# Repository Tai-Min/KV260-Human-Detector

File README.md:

# KV260-Human-Detector
Lidar based human detector on Kria KV260.

Created for [Adaptive Computing Challenge 2021
with Xilinx](https://www.hackster.io/contests/xilinxadaptivecomputing2021).

For more information about the project itself see [Human position estimator for mobile robots](https://www.hackster.io/Tai-Min/human-position-estimator-for-mobile-robots-d86454).

This repository contains all files and instructions required to recreate the project from scratch, including code, hardware design files, PCB design and 3D printable parts. 

# Recreating the project
## PCB shield

Use included in \<REPO>/pmod_shield/grbl Gerber files to order the shield using some PCB manufacturing service, or use included \<REPO>/pmod_shield/pcb.pdf to [etch it by yourself](https://www.instructables.com/How-to-Etch-a-PCB/).

For the parts you will need:
* 1x A4988 stepper motor driver,
* 2x 2 pin female JST PCB connectors,
* 1x 4 pin female JST PCB connector or 4x1 male vertical goldpin connector, whatever fits your stepper motor better,
* 1x 2x6 pin male horizontal goldpin connector,
* 2x 8x1 female vertical goldpin connectors,
* 1x 5.08mm screw terminal block

Solder the parts as in the picture below (ignore crossed parts):

## Attaching hardware
Print listed below parts (from \<REPO>/stl):
* 1x bottom_panel
* 1x bottom_panel_stopper
* 2x bottom_panel_feets
* 2x lidar_frame
* 1x motor_frame
* 2x top_panel
* 1x cradle
* lidar_board_holder
* 1x nema_connector

1) Screw 3D printed parts using M3 15mm screws,
2) Insert 608 bearings into bearing holes of lidar_frames,
3) Slide 190mm threaded rod through bearings and cradle (with M8 nuts inserted) into nema_connector,
5) Using M3 15mm screws and corresponding nuts, screw NEMA17 stepper motor, Creality endstops and YDlidar X4 
6) Slide KV260 into the frame,
7) Connect LIDAR through it's UART board to one of KV260's USB ports, 
8) Connect PMod shield to KV260 and then connect stepper motor and endstops to the shield.
9) Connect KV260 to PC and to local network using Ethernet connector.

Use these images for reference:

## Building the software
Project created and tested using Ubuntu-20.04.

This repo's root directory is from now onwards called \<REPO>

### Prerequisites

This instruction assumes that Vitis software (Vivado, Vitis, Vitis-AI, PetaLinux) runs on version 2021.1 and is correctly sourced in ".bashrc". It also assumes that PetaLinux has installed all [required packages](https://www.xilinx.com/support/documentation/sw_manuals/xilinx2020_1/ug1144-petalinux-tools-reference-guide.pdf).

For SD flashing [balenaEtcher](https://www.balena.io/etcher/) will be used.

Also, there are additional packages that should be installed via apt:
- putty
- sshpass (OPTIONAL used in build_app.sh with -p option provided to ignore multiple petalinux password inputs, considered bad practice so use at your own risk)

### Regenerate project

1. In Vivado open hardware project \<REPO>/hardware/hardware.xpr and press Generate Bitstream

Considering that build files for PetaLinux and it's SDK take roughly 60Gb of space, I don't think than anyone would want to download and extract such blob of files (also GitHub would be mad at me I guess). So to create this project locally I have provided simple script that builds everything from scratch up to the Vitis platform.

2. In terminal, in \<REPO>/ run:
```
chmod +x ./regenerate_hw.sh && ./regenerate_hw.sh
```
This script will:
- export hardware design (XSA file)
- generate and compile device tree overlay (DTO)
- compile pre-configured PetaLinux image, it's SDK and unpack it to Vitis workspace directory
- create .wic image for SD card
- update Vitis platform with new hardware description and linux image

3. Flash \<REPO>/linux/images/linux/petalinux-sdimage.wic into SD card (i.e using balenaEtcher)

4. Verify whether everything is working via Putty and set new petalinux's password (called \<DEVPWD> onwards):
```
sudo putty /dev/ttyUSBn -serial -sercfg 115200,8,n,1,N
```
replace "n" in "/dev/ttyUSBn" with correct USB number that responds with PetaLinux booting process.

Before leaving PetaLinux's shell, check device's ip with 
```
ifconfig
```
Write down address near "inet" under "eth0". This address will be called \<DEVIP> from now onwards.

### Build project
1. a) Only to build the application, in terminal, in \<REPO>/ run:
```
chmod +x ./build_app.sh && ./build_app.sh
```
This will generate all necessary files in \<REPO>/package/app/final

1. b) To build and upload to the device:
```
chmod +x ./build_app.sh && ./build_app.sh -u petalinux@<DEVIP>
```
This method will ask for petalinux's password multiple times.
1. c) (sshpass required!) To build and upload to the device:
```
chmod +x ./build_app.sh && ./build_app.sh -u petalinux@<DEVIP> -p <DEVPWD>
```
This method will ask for petalinux's password once.

### Run the application
1. a) SSH into KV260:
```
ssh petalinux@<DEVIP>
```

1. b) Use Putty terminal from previous steps.

2. Run:
```
sudo su
source ./setup.sh
./smart_lidar
```
* Sudo is required to use xmutil and access /lib folder.
* source.sh will setup FPGA bitstream and source ROS2 into our environment
* smart_lidar will start the application.

### Troubleshoting
If PetaLinux does not build due to error in Vitis-AI meta package, try to remove "dnndk" package from \<REPO>/linux/components/yocto/layers/meta-petalinux/recipes-core/packagegroups/packagegroup-petalinux-vitisai.bb

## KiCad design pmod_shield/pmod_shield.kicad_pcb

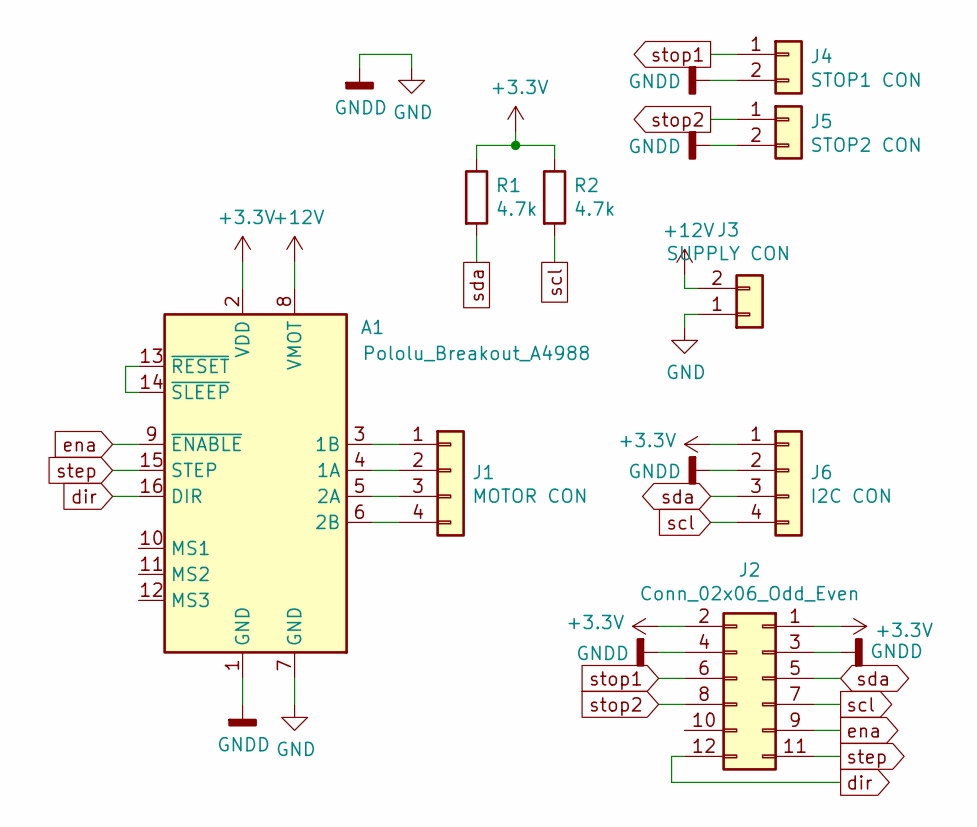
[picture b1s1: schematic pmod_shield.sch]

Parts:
A1: Pololu_Breakout_A4988; Pololu_Breakout-16_15.2x20.3mm
J1: MOTOR CON; PinHeader_1x04_P2.54mm_Vertical
J2: Conn_02x06_Odd_Even; PinHeader_2x06_P2.54mm_Horizontal
J3: SUPPLY CON; PhoenixContact_MSTBA_2,5_2-G-5,08_1x02_P5.08mm_Horizontal
J4: STOP1 CON; JST_XH_B2B-XH-AM_1x02_P2.50mm_Vertical
J5: STOP2 CON; JST_XH_B2B-XH-AM_1x02_P2.50mm_Vertical
J6: I2C CON; JST_XH_B4B-XH-AM_1x04_P2.50mm_Vertical
R1, R2: 4.7k; R_Axial_DIN0204_L3.6mm_D1.6mm_P7.62mm_Horizontal

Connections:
+3V3: A1.2 (VDD), J2.1, J2.2, J6.1, R1.1, R2.1
+12V: A1.8 (VMOT), J3.2
GND: A1.1 (GND), A1.7 (GND), J2.3, J2.4, J3.1, J4.2, J5.2, J6.2
unnamed: A1.3 (1B), J1.1
unnamed: A1.4 (1A), J1.2
unnamed: A1.5 (2A), J1.3
unnamed: A1.6 (2B), J1.4
unnamed: A1.13 (~RESET), A1.14 (~SLEEP)
dir: A1.16 (DIR), J2.12
ena: A1.9 (~ENABLE), J2.9
scl: J2.7, J6.4, R2.2
sda: J2.5, J6.3, R1.2
step: A1.15 (STEP), J2.11
stop1: J2.6, J4.1
stop2: J2.8, J5.1

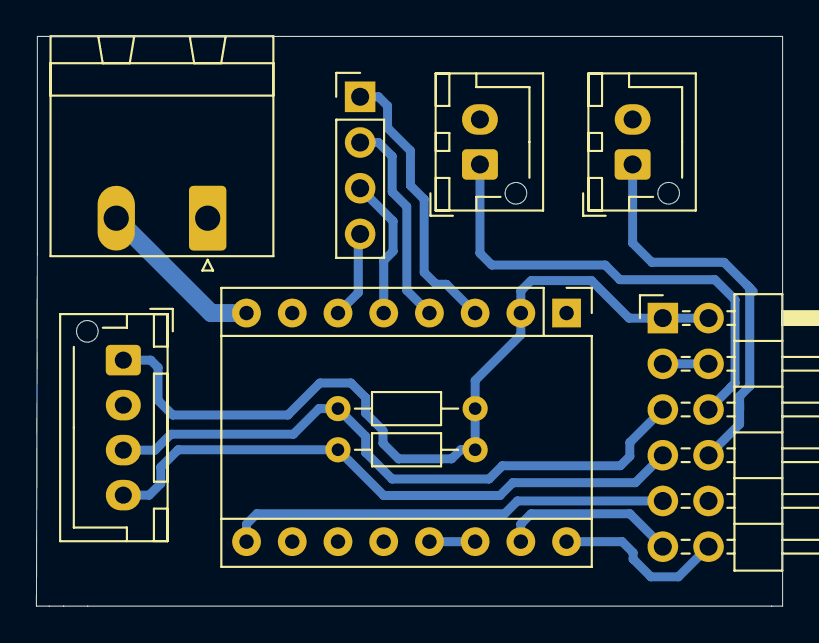
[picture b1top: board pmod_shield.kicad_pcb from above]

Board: 2 copper layers, 41.5 x 31.6 mm, 9 parts (0 on the bottom side), 15 nets.

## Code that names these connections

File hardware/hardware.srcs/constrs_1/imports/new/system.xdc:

set_property PACKAGE_PIN B11 [get_ports stop1]
set_property IOSTANDARD LVCMOS33 [get_ports stop1]
set_property PULLTYPE PULLUP [get_ports stop1]

set_property PACKAGE_PIN D11 [get_ports stop2]
set_property IOSTANDARD LVCMOS33 [get_ports stop2]
set_property PULLTYPE PULLUP [get_ports stop2]

set_property PACKAGE_PIN H12 [get_ports step]
set_property IOSTANDARD LVCMOS33 [get_ports step]

set_property PACKAGE_PIN B10 [get_ports dir]
set_property IOSTANDARD LVCMOS33 [get_ports dir]

set_property PACKAGE_PIN E10 [get_ports ena]
set_property IOSTANDARD LVCMOS33 [get_ports ena]

set_property PACKAGE_PIN A12 [get_ports fan]
set_property IOSTANDARD LVCMOS33 [get_ports fan]

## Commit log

2022-01-09 Create HW design
2022-01-09 Add linux conf
2022-01-09 Work on build script, generate FPGA bitstream
2022-01-09 Work on build_linux.ps1 script
2022-01-12 Add build_app.ps1, work on regenerate_hw.ps1
2022-01-18 Moving to linux
2022-01-18 Move to linux
2022-01-18 Modify gitignore
2022-01-18 Fix ignores
2022-01-18 Remove files
2022-02-01 Move HW design to Vivado 2020.2 for KRS stack
2022-02-07 Env setup for project
2022-02-07 Control stepper from app
2022-02-07 Add ydlidar sdk
2022-02-10 Add USB Hub to DeviceTree
2022-02-13 Add working PointCloud2 generation!
2022-02-13 Remove ROS dir
2022-02-15 Add working lidar processing kernel
2022-02-16 Cleanup
2022-02-23 Add quantized network
    Former-commit-id: a3f06d4bef5145aff5dc18ba74af4e75b19ae95a
2022-02-23 Add quantized network
    Former-commit-id: 3d71c2cf671913765ee814f8c39f16e2e66f0495
2022-02-23 Add quantized network
    Former-commit-id: d6f0727b01074878700e8908f3f9420d18663911
2022-02-23 Add quantized network
    Former-commit-id: ac82a5ffe366e01a9225eca417aa951a286c4043
2022-02-23 Add quantized network
    Former-commit-id: 2e93fe863f3f042f3845f770757ea0587df8208d
2022-02-23 Add quantized network
    Former-commit-id: 686149732d91c289f4d13bb343f18ecc6e9f5a94
2022-02-23 Add quantized network
    Former-commit-id: 7323220f74a38ff7bd91f414d766675e5889831a
2022-03-03 Fix padding
    Former-commit-id: 0b71f26b0f5eeac8cc3295633aa7daf47227497f
    Former-commit-id: a1b3f106a05651add333338576ab2586ceb8ca72
2022-03-03 Remove big files
    Former-commit-id: ff0ec5e7707b4a806fe689360f8f8497f345172e
    Former-commit-id: 99863fd4afc6455dcaf9f85f848ad82fe09fa53a
2022-03-03 Remove big files
    Former-commit-id: 4294142ea242a54f780d29b77170d1c28d5a4166
    Former-commit-id: 56d9dbb9bf90043c87825a3eb920d51f584fe444
2022-03-03 Remove big files
    Former-commit-id: 3235686a7cda953ef8d3e124c11809c804115caf
    Former-commit-id: b5cd088677cb0b477f1ccc54a4f2a19dc7ec4fcf
2022-03-03 Remove big files
    Former-commit-id: 2cfd0db9969287dc6372535a081b111af909ffd6
    Former-commit-id: 9c8b8d033b59f036dde3cc2b83e69980811f3604
2022-03-03 Remove big files
    Former-commit-id: 834c30d61183f8875c17821ff1f847ef550b935e
2022-03-03 Regenerate platform
2022-03-03 Update README, add gerber and stl files
2022-03-03 Fix schematic.jpg
2022-03-04 Add xmodel
2022-03-23 Add working dpcma, dpu drivers and working inference engine
2022-03-25 Add projection to cloud kernel
2022-03-29 Code cleanup
2022-03-29 Uncomment some code
2022-03-29 Small fixes
2022-03-30 Create LICENSE
